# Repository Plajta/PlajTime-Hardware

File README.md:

# PlajTime Hardware
This repository has the full history of PlajTime hardware development.
Before 19.9.2025 development took place in a single private repository and it was starting to be a little bit messy.
With beginning work on PlajTime's second prototype we made the decision to split the repos and make the code and design finally available.

## What about the older versions?
Every "release" will have it's own tag so you (and we) can look at the older versions and laugh how bad at engineering we are.

## License

This project is licensed under the [Creative Commons Attribution-NonCommercial-ShareAlike 4.0 International License](https://creativecommons.org/licenses/by-nc-sa/4.0/).

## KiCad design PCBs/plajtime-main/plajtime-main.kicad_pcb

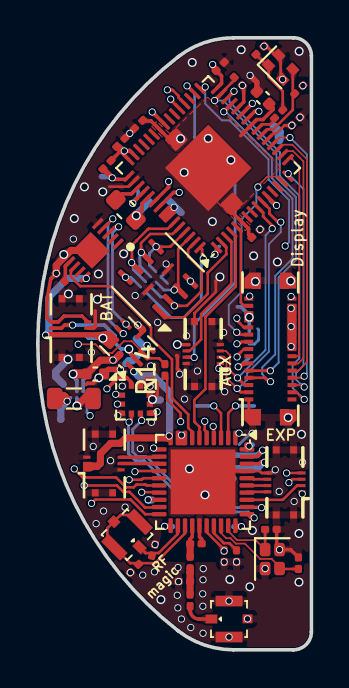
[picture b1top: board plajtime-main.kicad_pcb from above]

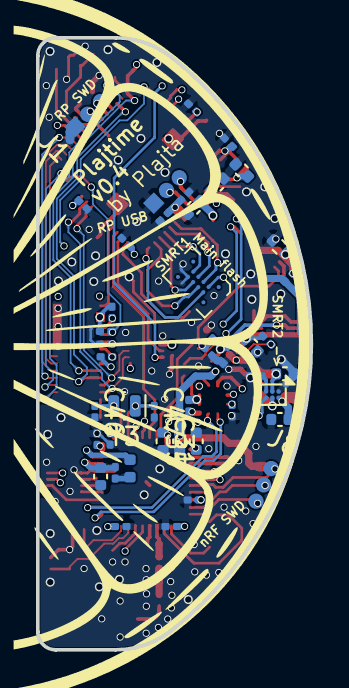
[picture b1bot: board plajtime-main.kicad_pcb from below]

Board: 6 copper layers, 15.2 x 34.0 mm, 85 parts (44 on the bottom side), 80 nets.

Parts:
C1, C6, C8, C9, C12, C17, C31, C35, C41, C43: 4.7uF; C_0402_1005Metric
C2, C29, C42: 1uF; C_0201_0603Metric
C3, C4: 15pF_H; C_0201_0603Metric
C5, C7, C10, C11, C14, C16, C18, C19, C20, C21, C22, C23, C24, C25, C27, C30, C36, C38, C39: 0.1uF; C_0201_0603Metric
C13, C15: 10uF; C_0402_1005Metric
C26: 0.47uF; C_0201_0603Metric
C32, C33: 12pF_H; C_0201_0603Metric
C34: 1.2pF_H; C_0201_0603Metric
C37: 1pF_H; C_0201_0603Metric
C40: 820pF; C_0201_0603Metric
C44, C45: 270pF_H; C_0201_0603Metric
C46, C47: TBD; C_0201_0603Metric
J1: RP SWD; PinHeader_1x03_P1.00mm_Vertical
J2: RP USB; PinHeader_1x03_P1.00mm_Vertical
J4: Display connector; ConnectorDisplay-30
J5: Extention connector; 5050660822
J6, J9: Conn_Coaxial; W.FL_Hirose_W.FL2-R-SMT-1_Vertical
J7: Battery Connector; CONN_505066-0622_MOL
J8: Nordic SWD; PinHeader_1x03_P1.00mm_Vertical_1
J10: Internal connector; 5050660822
J11: USB; CONN_505066-0622_MOL
L1: 3.3uH; L_0603_1608Metric
L2: 1uH; L_0805_2012Metric
L3: 2.2nH; R_0201_0603Metric
L4: 4.7nH; L_0201_0603Metric
L5: 15nH; L_0201_0603Metric
L6: 10uH; L_0402_1005Metric
R1: 7.32k; R_0201_0603Metric
R2: 133k; R_0201_0603Metric
R3: 33; R_0201_0603Metric
R4: 1k; R_0201_0603Metric
R5: 10m; R_0402_1005Metric
R8, R9, R10, R11, R12: 10k; R_0201_0603Metric
R13, R14: TBD; R_0201_0603Metric
U1: W25Q64JWUUIQ; Winbond_USON-8-2EP_3x4mm_P0.8mm_EP0.2x0.8mm
U2: W25Q64JWBYIM; BGA-24_4x6_6.0x6.0mm
U3: TPS628438YKA; Texas_DSBGA-6_0.757x1.01mm_Layout2x3_P0.35mm
U4: MP2664; MPS_MP2664_QFN-10_2x2mm_P0.5mm
U5: RP2350A; QFN-60-1EP_7x7mm_P0.4mm_EP3.4x3.4mm
U6: BMA456; LGA-12_2x2mm_P0.5mm
U7: MAX17055; SON40P250X200X80-11N
U9: nRF52833_QDxx; QFN-40-1EP_5x5mm_P0.4mm_EP3.6x3.6mm
Y1: 13MHz; Oscillator_SMD_Abracon_ASCO-4Pin_1.6x1.2mm
Y2: 32MHz; Crystal_SMD_WE_IQXC-26-4Pin_1.6x1.2mm
Y3: 32.768kHz Crystal; Crystal_SMD_MicroCrystal_CM9V-T1A-2Pin_1.6x1.0mm

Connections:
+1V1: C5.1, C8.1, C9.1, C10.1, L1.1, U5.6 (DVDD), U5.23 (DVDD), U5.39 (DVDD), U5.50 (VREG_FB)
+3V: C6.1, C11.1, C14.1, C15.1, C16.1, C18.1, C19.1, C20.1, C21.1, C23.1, C24.1, C25.1, C27.1, C29.1, C30.1, C31.1, C36.1, J4.11, J4.23, J4.25, J4.29, J4.30, J5.1, J10.1, L2.2, R3.1, R8.1, R9.1, R10.1, R11.1, U1.8 (VCC), U2.B2 (VCC), U3.A2 (VOS), U5.1 (IOVDD), U5.11 (IOVDD), U5.20 (IOVDD), U5.26 (RUN), U5.30 (IOVDD), U5.38 (IOVDD), U5.44 (ADC_AVDD), U5.45 (IOVDD), U5.49 (VREG_VIN), U5.53 (USB_OTP_VDD), U5.54 (QSPI_IOVDD), U6.3 (VDDIO), U6.7 (VDD), U6.10 (CSB), U9.8 (VDD), U9.9 (VDDH), U9.18 (VDD), U9.30 (VDD), U9.40 (VDD)
+5V: C2.1, C41.1, J11.1, J11.3, U4.1 (IN), U9.10 (VBUS)
+BATT: C17.1, C22.1, J7.1, J7.2, R13.1, U4.8 (BATT), U4.9 (BATT), U7.10 (BATT)
-BATT: C22.2, C26.2, J7.5, J7.6, R5.1, U7.6 (CSP), U7.11 (CSP)
/BATT_NTC: J7.3, R1.2, U4.2 (NTC)
/CHARGER_INT: R14.1, U9.17 (P0.20)
/CHG_VDD: C7.1, R1.1, U4.4 (VDD)
/DEC_4_6: C42.1, C43.1, L5.1, U9.26 (DEC6), U9.38 (DEC4)
/DISP_CS: J4.6, U5.15 (GPIO11)
/DISP_DI1: J4.12, U5.17 (GPIO13)
/DISP_DI2: J4.10, U5.18 (GPIO14)
/DISP_DI3: J4.8, U5.19 (GPIO15)
/DISP_DIO0: J4.14, U5.16 (GPIO12)
/DISP_EN: J4.21, R9.2, U5.31 (GPIO19)
/DISP_IM0: J4.17, R12.1
/DISP_IM1: J4.15, R10.2
/DISP_RST: J4.19, R8.2, U5.14 (GPIO10)
/DISP_SCL: J4.4, U5.28 (GPIO17)
/DISP_TE: J4.27, U5.5 (GPIO3)
/EXT_GPIO_1: J5.6, U9.36 (AIN7/P0.31)
/EXT_GPIO_2: J5.3, U9.33 (AIN4/P0.28)
/EXT_INT: J5.2, U9.34 (AIN5/P0.29)
/EXT_RST: J5.4, U9.35 (AIN6/P0.30)
/GAUGE_INT: U7.8 (ALRT), U9.7 (P0.11)
/IMU_INT_1: U6.5 (INT1), U9.31 (AIN1/P0.03)
/IMU_INT_2: U6.6 (INT2), U9.32 (AIN0/P0.02)
/NRF_DECUSB: C35.1, U9.11 (DECUSB)
/NRF_SWDCLK: J8.2, U9.19 (SWDIO)
/NRF_SWDIO: J8.3, U9.20 (SWDCLK)
/NRF_SWDRST: J8.1, U9.16 (P0.18/~RESET)
/NRF_XL1: C46.1, U9.2 (XL1/P0.00), Y3.2
/NRF_XL2: C47.1, U9.3 (XL2/P0.01), Y3.1
/QMI_CS0: U2.B3 (~CS), U5.60 (QSPI_SS)
/QMI_CS1: U1.1 (~CS), U5.2 (GPIO0)
/QMI_SCLK: U1.6 (CLK), U2.D2 (CLK), U5.56 (QSPI_SCLK)
/QMI_SD0: U1.5 (DI/IO_{0}), U2.E2 (DI/IO_{0}), U5.57 (QSPI_SD0)
/QMI_SD1: U1.2 (DO/IO_{1}), U2.C3 (DO/IO_{1}), U5.59 (QSPI_SD1)
/QMI_SD2: U1.3 (~WP/IO_{2}), U2.D3 (~WP/IO_{2}), U5.58 (QSPI_SD2)
/QMI_SD3: U1.7 (~HOLD/~RESET/IO_{3}), U2.C2 (~HOLD/~RESET/IO_{3}), U5.55 (QSPI_SD3)
/RP_SWDCLK: J1.2, U5.24 (SWCLK)
/RP_SWDIO: J1.3, U5.25 (SWDIO)
/RP_USB_D+: J2.2, U5.52 (USB_DP)
/RP_USB_D-: J2.3, U5.51 (USB_DM)
/SLIDER_INT: J10.6, U5.3 (GPIO1)
/TP_INT: J4.7, U5.27 (GPIO16)
/TP_RESET: J4.9, R11.2, U5.29 (GPIO18)
/VIC_INT: J10.4, U5.32 (GPIO20)
/XIN: C3.1, U5.21 (XIN), Y1.3
/XOUT: R4.2, U5.22 (XOUT)
GND: C1.2, C2.2, C3.2, C4.2, C5.2, C6.2, C7.2, C8.2, C9.2, C10.2, C11.2, C12.2, C13.2, C14.2, C15.2, C16.2, C17.2, C18.2, C19.2, C20.2, C21.2, C23.2, C24.2, C25.2, C27.2, C29.2, C30.2, C31.2, C32.2, C33.2, C34.2, C35.2, C36.2, C37.2, C38.2, C39.2, C40.2, C41.2, C42.2, C43.2, C44.2, C45.2, C46.2, C47.2, J1.1, J2.1, J4.1, J4.16, J4.18, J4.20, J4.22, J4.24, J4.26, J4.28, J4.31 (MP), J5.8, J5.MP (MountPin), J6.2 (Ext), J7.4, J7.MP (MountPin), J10.2, J10.7, J10.MP (MountPin), J11.2, J11.5, J11.MP (MountPin), R2.2, R5.2, R12.2, U1.4 (GND), U1.9 (EP), U2.E3 (GND), U3.A1 (GND), U4.5 (GND), U5.47 (VREG_PGND), U5.61 (GND), U6.1 (SDO), U6.4 (ASDA), U6.8 (GNDIO), U6.9 (GND), U6.11 (ASCL), U7.5 (CSN), U9.25 (VSS_PA), U9.37 (VSS), U9.41 (VSS), Y1.2 (G), Y1.4 (G), Y2.2 (G), Y2.4 (G)
GPU_INT: U5.4 (GPIO2), U9.6 (P1.09)
unnamed: C4.1, R4.1, Y1.1
unnamed: C26.1, U7.7 (REG)
unnamed: C34.1, L3.2, L4.1
unnamed: J6.1 (In), L3.1
unnamed: C45.1, J9.2 (Ext), U9.23 (NFC2/P0.10)
unnamed: C44.1, J9.1 (In), U9.22 (NFC1/P0.09)
unnamed: L5.2, L6.1
unnamed: L2.1, U3.B2 (SW)
unnamed: R2.1, U3.C1 (VSET)
unnamed: R13.2, R14.2, U4.3 (INT)
unnamed: C12.1, R3.2, U5.46 (VREG_AVDD)
unnamed: L1.2, U5.48 (VREG_LX)
unnamed: C37.1, L4.2, U9.24 (ANT)
unnamed: L6.2, U9.39 (DCC)
unnamed: C39.1, U9.1 (DEC1)
unnamed: C38.1, U9.27 (DEC3)
unnamed: C40.1, U9.21 (DEC5)
unnamed: C32.1, U9.28 (XC1), Y2.3
unnamed: C33.1, U9.29 (XC2), Y2.1
RP_SCL: J4.3, J10.3, U5.10 (GPIO7)
RP_SDA: J4.5, J10.5, U5.9 (GPIO6)
SCL: J5.7, U4.6 (SCL), U6.12 (SCX), U7.3 (SCL), U9.4 (AIN2/P0.04)
SDA: J5.5, U4.7 (SDA), U6.2 (SDX), U7.4 (SDA), U9.5 (AIN3/P0.05)
UART_RX: U5.35 (GPIO23), U9.15 (P0.17)
UART_TX: U5.34 (GPIO22), U9.14 (P0.15)
USB_D+: J11.6, U9.12 (D-)
USB_D-: J11.4, U9.13 (D+)
VSYS: C1.1, C13.1, J10.8, U3.B1 (VIN), U3.C2 (EN), U4.10 (SYS)

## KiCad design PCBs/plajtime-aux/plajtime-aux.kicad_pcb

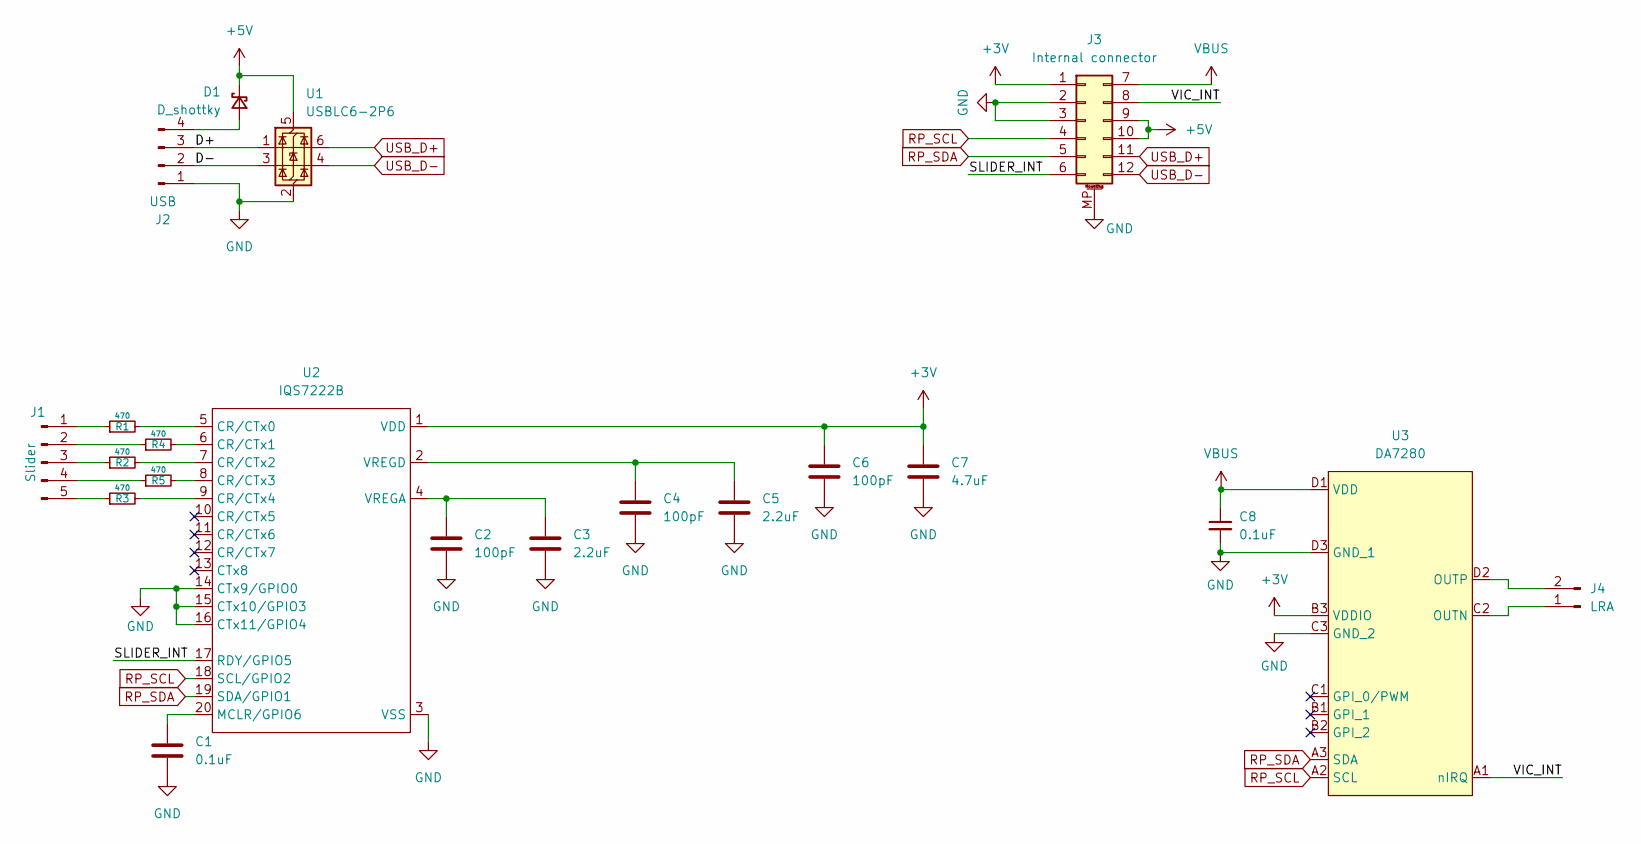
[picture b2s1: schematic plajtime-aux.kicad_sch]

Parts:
C1, C8: 0.1uF; C_0201_0603Metric; LCSC_Part C161494
C2, C4, C6: 100pF; C_0201_0603Metric; LCSC_Part C541236
C3, C5: 2.2uF; C_0201_0603Metric; Mouser 81-GRM033R61A225KE7D
C7: 4.7uF; C_0402_1005Metric; LCSC_Part C23733
D1: D_shottky; D_0402_1005Metric; LCSC_Part C94366
J1: Slider; TouchSlider-5_25.0248x4.2mm
J2: USB; PinHeader_1x04_P2.54mm_Vertical
J3: Internal connector; 5050701222; Mouser 538-505070-1222
J4: LRA; PinHeader_1x02_P1.00mm_Vertical
R1, R2, R3, R4, R5: 470; R_0201_0603Metric; LCSC_Part C18164334
U1: USBLC6-2P6; PESD3V3L5UF115; LCSC_Part C478118
U2: IQS7222B; QFN-20-1EP_3x3mm_P0.4mm_EP1.65x1.65mm; Mouser 957-IQS7222B102QNR
U3: DA7280; BGA12C40P3X4_135X175X58; Mouser 724-DA7280-00V42

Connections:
+3V: C6.1, C7.1, J3.1, U2.1 (VDD), U3.B3 (VDDIO)
+5V: D1.1 (K), J3.9, J3.10, U1.5 (VBUS)
/D+: J2.3, U1.1 (I/O1)
/D-: J2.2, U1.3 (I/O2)
/SLIDER_INT: J3.6, U2.17 (RDY/GPIO5)
/VIC_INT: J3.8, U3.A1 (nIRQ)
GND: C1.2, C2.2, C3.2, C4.2, C5.2, C6.2, C7.2, C8.2, J2.1, J3.2, J3.3, J3.MP (MountPin), U1.2 (GND), U2.3 (VSS), U2.14 (CTx9/GPIO0), U2.15 (CTx10/GPIO3), U2.16 (CTx11/GPIO4), U2.21 (EP), U3.C3 (GND_2), U3.D3 (GND_1)
unnamed: D1.2 (A), J2.4
unnamed: J1.1, R1.1
unnamed: J1.2, R4.1
unnamed: J1.3, R2.1
unnamed: J1.4, R5.1
unnamed: J1.5, R3.1
unnamed: J4.1, U3.C2 (OUTN)
unnamed: J4.2, U3.D2 (OUTP)
unnamed: R1.2, U2.5 (CR/CTx0)
unnamed: R4.2, U2.6 (CR/CTx1)
unnamed: R2.2, U2.7 (CR/CTx2)
unnamed: R5.2, U2.8 (CR/CTx3)
unnamed: R3.2, U2.9 (CR/CTx4)
unnamed: C1.1, U2.20 (MCLR/GPIO6)
unnamed: C2.1, C3.1, U2.4 (VREGA)
unnamed: C4.1, C5.1, U2.2 (VREGD)
RP_SCL: J3.4, U2.18 (SCL/GPIO2), U3.A2 (SCL)
RP_SDA: J3.5, U2.19 (SDA/GPIO1), U3.A3 (SDA)
USB_D+: J3.11, U1.6 (I/O1)
USB_D-: J3.12, U1.4 (I/O2)
VBUS: C8.1, J3.7, U3.D1 (VDD)

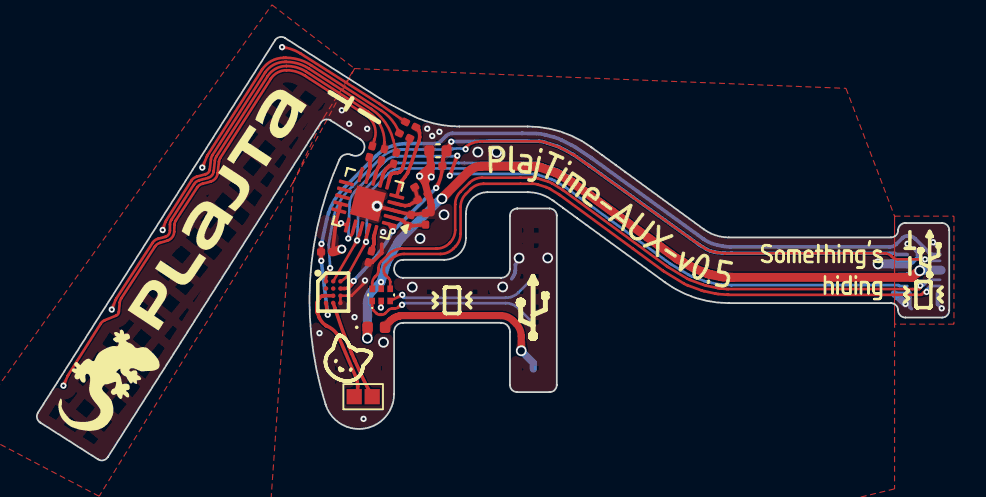
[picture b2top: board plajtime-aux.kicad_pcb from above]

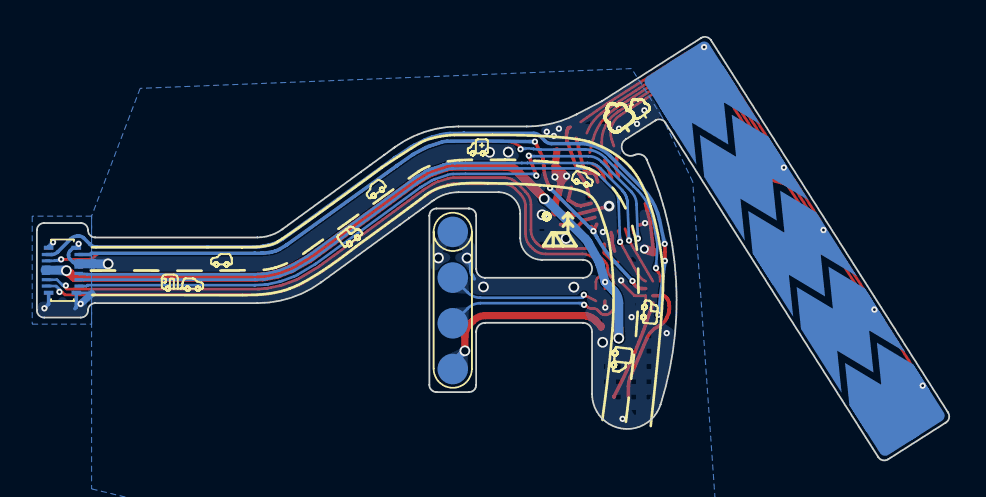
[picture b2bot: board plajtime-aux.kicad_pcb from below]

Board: 2 copper layers, 50.7 x 23.5 mm, 21 parts (3 on the bottom side), 28 nets.

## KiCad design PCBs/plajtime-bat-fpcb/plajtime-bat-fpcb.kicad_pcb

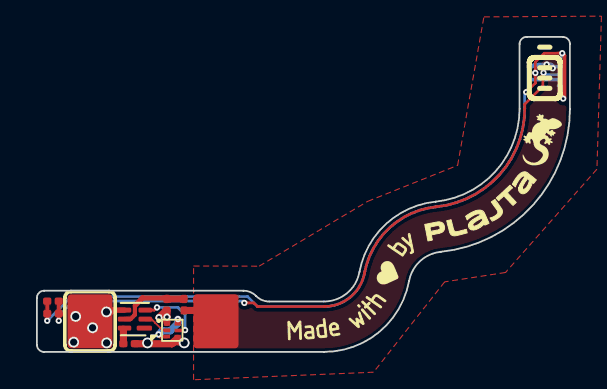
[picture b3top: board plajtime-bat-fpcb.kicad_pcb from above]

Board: 2 copper layers, 29.6 x 17.5 mm, 9 parts (1 on the bottom side), 10 nets.

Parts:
BT1: Battery_Cell; Battery
C1: 0.1uF; C_0201_0603Metric
J7: Battery Connector; CONN_505070-0622_MOL
Q1: NX7002BKXBZ; DFN1010B-6
R1: 330; R_0201_0603Metric
R2: 2.2k; R_0201_0603Metric
R3: 26.1k; R_0201_0603Metric
TH1: Thermistor_NTC; R_0201_0603Metric
U1: BQ297xy; WSON-6_1.5x1.5mm_P0.5mm

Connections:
+BATT: BT1.1 (+), J7.1, J7.2, R1.1
-BATT: J7.5, J7.6, Q1.4 (S), R2.2
-CELL: BT1.2 (-), C1.2, Q1.1 (S), U1.4 (VSS)
/BATT_NTC: J7.3, R3.2, TH1.1
GND: J7.4, J7.MP (MountPin), R3.1, TH1.2
unnamed: Q1.3 (D), Q1.6 (D)
unnamed: Q1.2 (G), U1.2 (Cout)
unnamed: Q1.5 (G), U1.3 (Dout)
unnamed: C1.1, R1.2, U1.5 (BAT)
unnamed: R2.1, U1.6 (V-)

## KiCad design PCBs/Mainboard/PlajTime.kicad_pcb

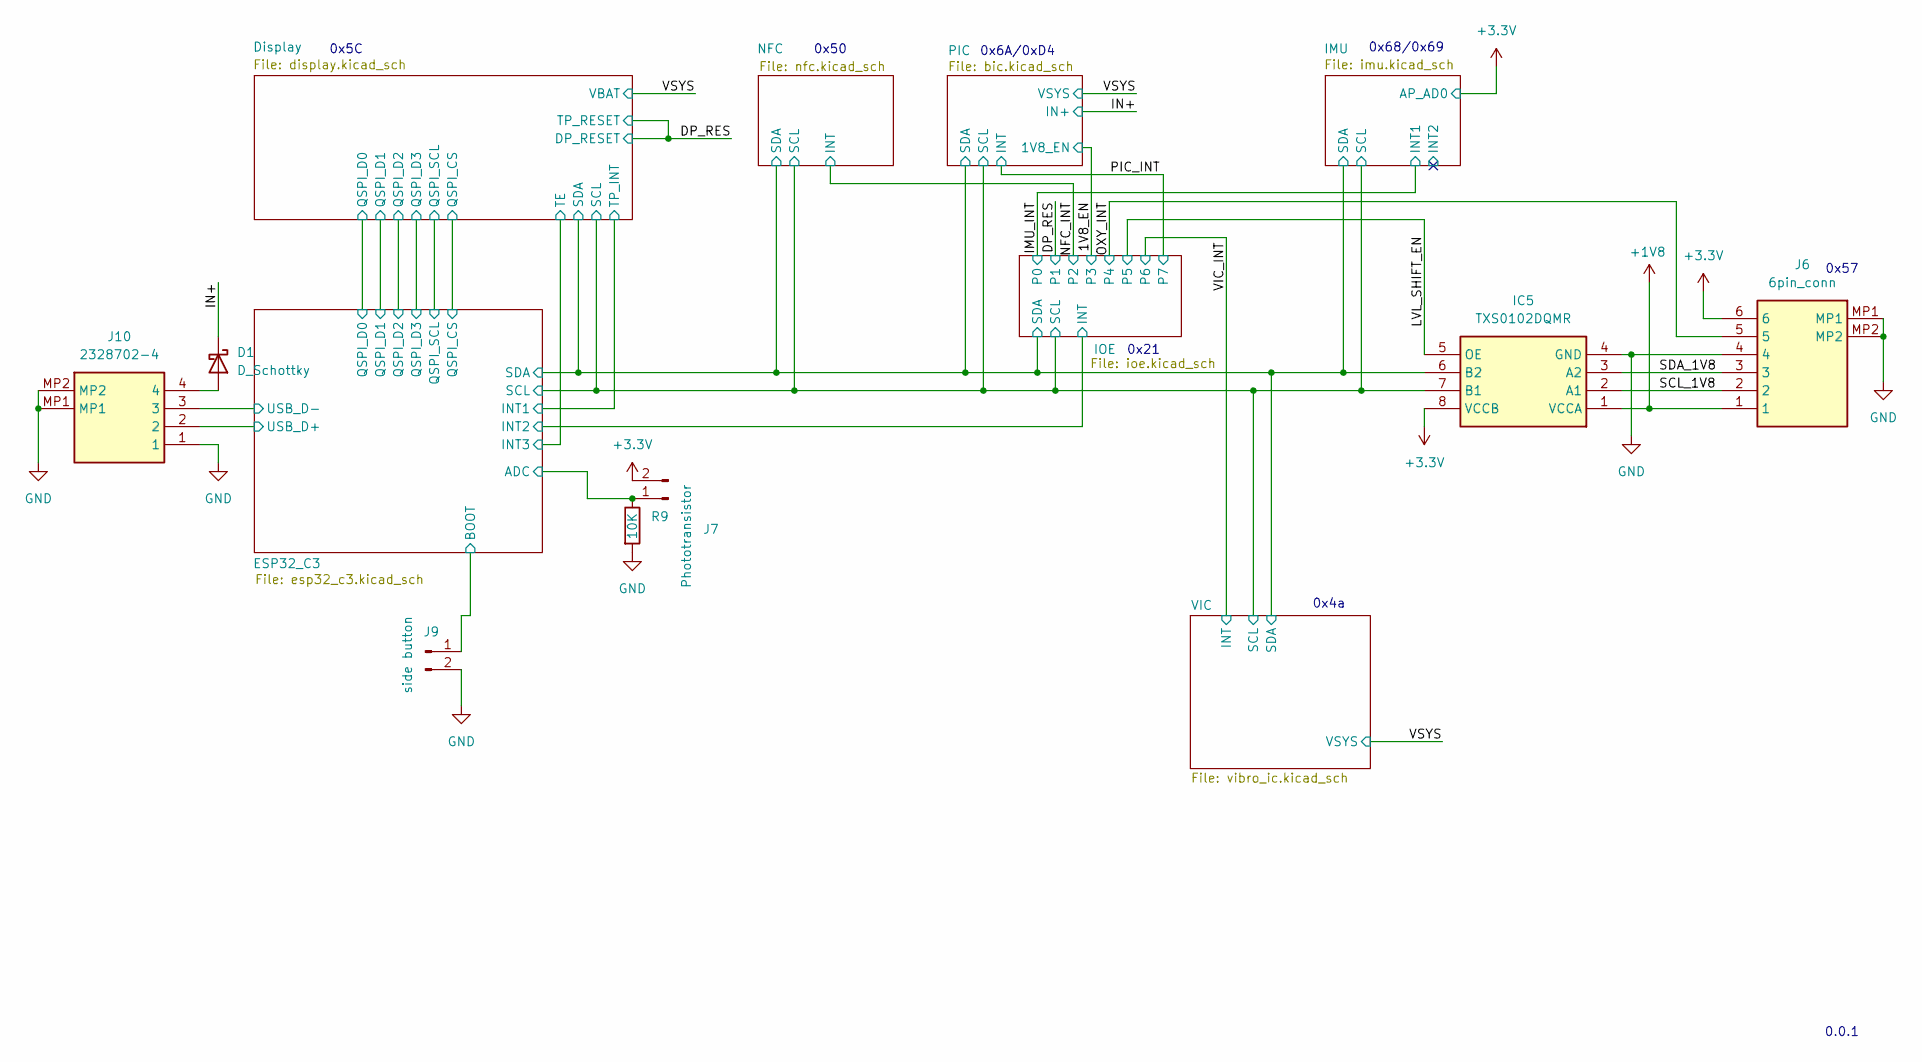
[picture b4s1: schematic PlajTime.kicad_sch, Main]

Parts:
D1: D_Schottky; D_0603_1608Metric
IC5: TXS0102DQMR; SON40P120X180X40-8N; Mouser Part Number 595-TXS0102DQMR
J6: 6pin_conn; Mouser Part Number 571-2328702-6
J7: Phototransistor; PinHeader_1x02_P1.00mm_Vertical
J9: side button; PinHeader_1x02_P1.00mm_Vertical
J10: 2328702-4; 23287024; Mouser Part Number 571-2328702-4
R9: 10K; R_0201_0603Metric

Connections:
+1V8: IC5.1 (VCCA), J6.1; also elsewhere on the board
+3.3V: IC5.8 (VCCB), J6.6, J7.2; also elsewhere on the board
/Display/SCL: IC5.7 (B1); also elsewhere on the board
/Display/SDA: IC5.6 (B2); also elsewhere on the board
/ESP32_C3/ADC: J7.1, R9.1; also elsewhere on the board
/ESP32_C3/BOOT: J9.1; also elsewhere on the board
/ESP32_C3/USB_D+: J10.2; also elsewhere on the board
/ESP32_C3/USB_D-: J10.3; also elsewhere on the board
/IN+: D1.1 (K); also elsewhere on the board
/LVL_SHIFT_EN: IC5.5 (OE); also elsewhere on the board
/OXY_INT: J6.5; also elsewhere on the board
/SCL_1V8: IC5.2 (A1), J6.2
/SDA_1V8: IC5.3 (A2), J6.3
GND: IC5.4 (GND), J6.4, J6.MP1, J6.MP2, J9.2, J10.1, J10.MP1, J10.MP2, R9.2; also elsewhere on the board
unnamed: D1.2 (A), J10.4

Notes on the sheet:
0.0.1
0x21
0x5C
0x68/0x69
0x57
0x6A/0xD4
0x4a
0x50

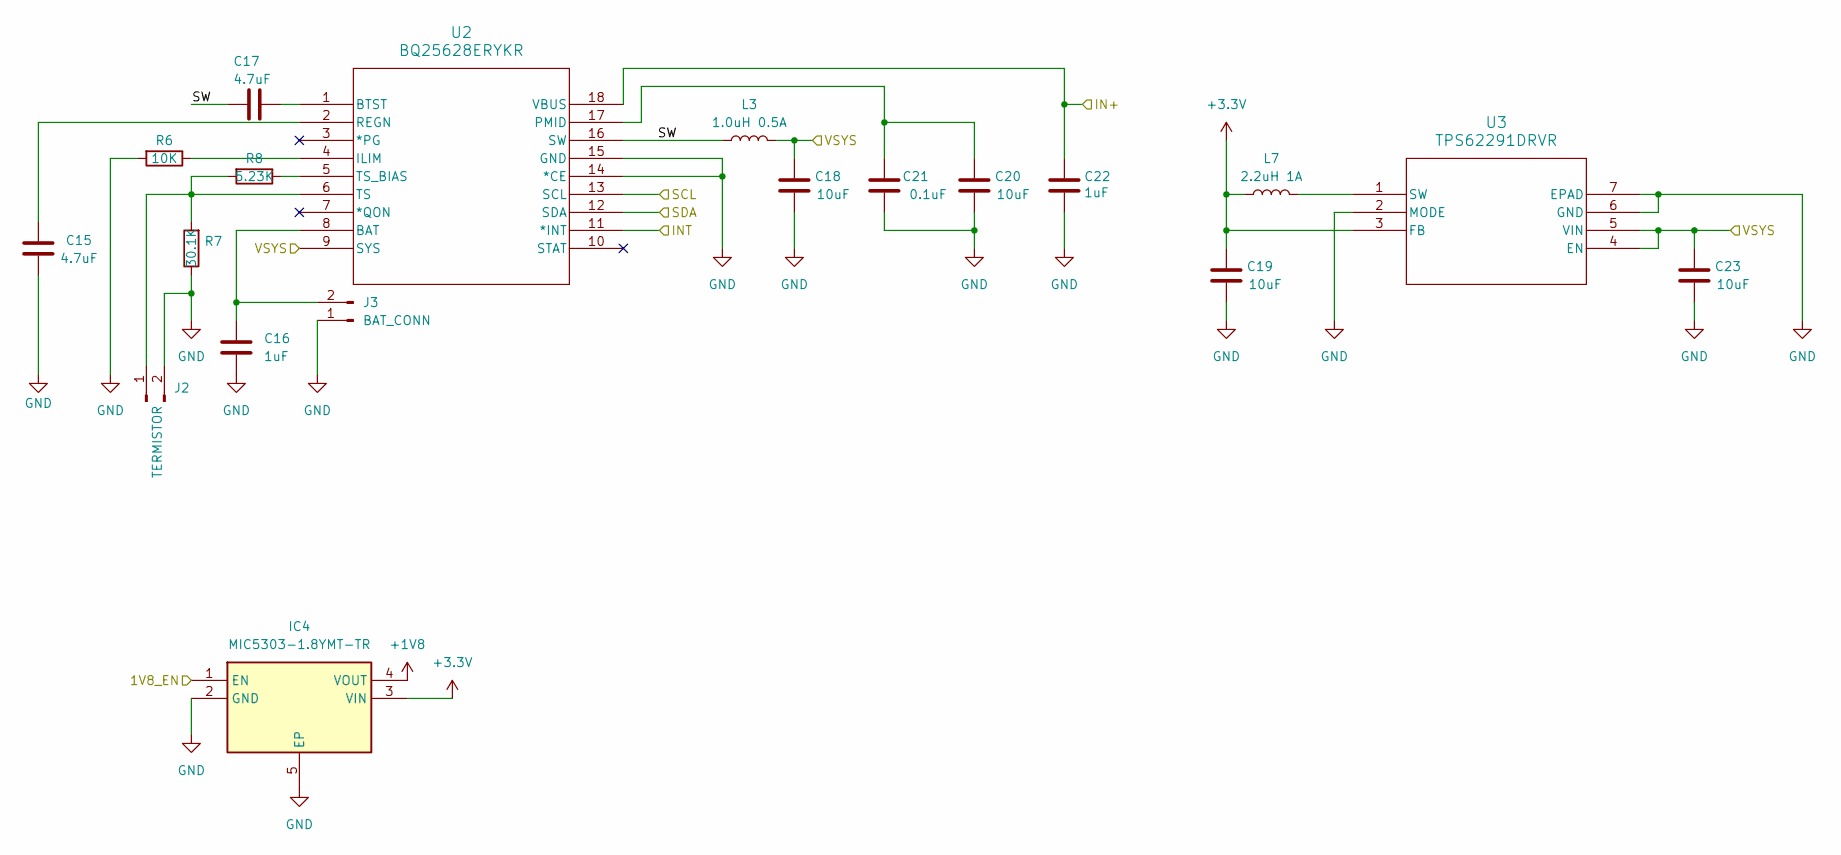
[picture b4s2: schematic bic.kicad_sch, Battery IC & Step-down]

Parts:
C15, C17: 4.7uF; C_0201_0603Metric
C16, C22: 1uF; C_0201_0603Metric
C18, C19, C20, C23: 10uF; C_0402_1005Metric
C21: 0.1uF; C_0201_0603Metric
IC4: MIC5303-1.8YMT-TR; SON50P160X120X60-5N-D; Mouser Part Number 998-MIC5303-1.8YMTTR
J2: TERMISTOR; PinHeader_1x02_P1.00mm_Vertical
J3: BAT_CONN; BattSolderPads
L3: 1.0uH 0.5A; L_0402_1005Metric
L7: 2.2uH 1A; L_0603_1608Metric
R6: 10K; R_0201_0603Metric
R7: 30.1K; R_0201_0603Metric
R8: 5.23K; R_0201_0603Metric
U2: BQ25628ERYKR; WQFN-HR18__RYK_TEX
U3: TPS62291DRVR; DRV6_1P6X1

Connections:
+1V8: IC4.4 (VOUT); also elsewhere on the board
+3.3V: C19.1, IC4.3 (VIN), L7.1, U3.3 (FB); also elsewhere on the board
/1V8_EN: IC4.1 (EN); also elsewhere on the board
/Display/SCL: U2.13 (SCL); also elsewhere on the board
/Display/SDA: U2.12 (SDA); also elsewhere on the board
/IN+: C22.1, U2.18 (VBUS); also elsewhere on the board
/PIC/SW: C17.1, L3.1, U2.16 (SW)
/PIC_INT: U2.11 (*INT); also elsewhere on the board
/VSYS: C18.1, C23.1, L3.2, U2.9 (SYS), U3.4 (EN), U3.5 (VIN); also elsewhere on the board
GND: C15.1, C16.2, C18.2, C19.2, C20.2, C21.2, C22.2, C23.2, IC4.2 (GND), IC4.5 (EP), J2.2, J3.1, R6.2, R7.1, U2.14 (*CE), U2.15 (GND), U3.2 (MODE), U3.6 (GND), U3.7 (EPAD); also elsewhere on the board
unnamed: J2.1, R7.2, R8.2, U2.6 (TS)
unnamed: C16.1, J3.2, U2.8 (BAT)
unnamed: C17.2, U2.1 (BTST)
unnamed: R6.1, U2.4 (ILIM)
unnamed: C20.1, C21.1, U2.17 (PMID)
unnamed: C15.2, U2.2 (REGN)
unnamed: R8.1, U2.5 (TS_BIAS)
unnamed: L7.2, U3.1 (SW)

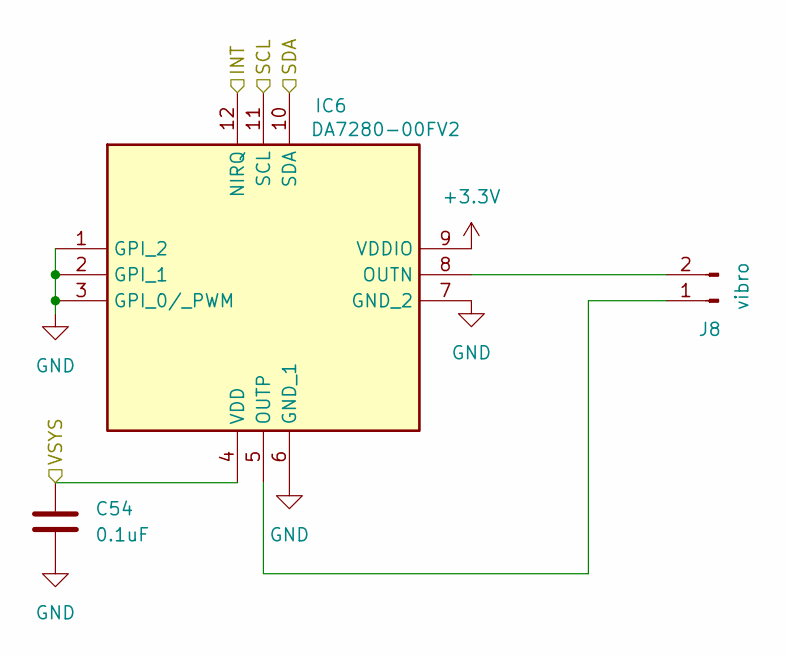
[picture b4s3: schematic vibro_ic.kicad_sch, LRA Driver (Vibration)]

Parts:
C54: 0.1uF; C_0201_0603Metric
IC6: DA7280-00FV2; QFN65P300X300X84-12N; Mouser Part Number 724-DA7280-00FV2
J8: vibro; PinHeader_1x02_P1.00mm_Vertical

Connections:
+3.3V: IC6.9 (VDDIO); also elsewhere on the board
/Display/SCL: IC6.11 (SCL); also elsewhere on the board
/Display/SDA: IC6.10 (SDA); also elsewhere on the board
/VIC_INT: IC6.12 (NIRQ); also elsewhere on the board
/VSYS: C54.1, IC6.4 (VDD); also elsewhere on the board
GND: C54.2, IC6.1 (GPI_2), IC6.2 (GPI_1), IC6.3 (GPI_0/_PWM), IC6.6 (GND_1), IC6.7 (GND_2); also elsewhere on the board
unnamed: IC6.8 (OUTN), J8.2
unnamed: IC6.5 (OUTP), J8.1

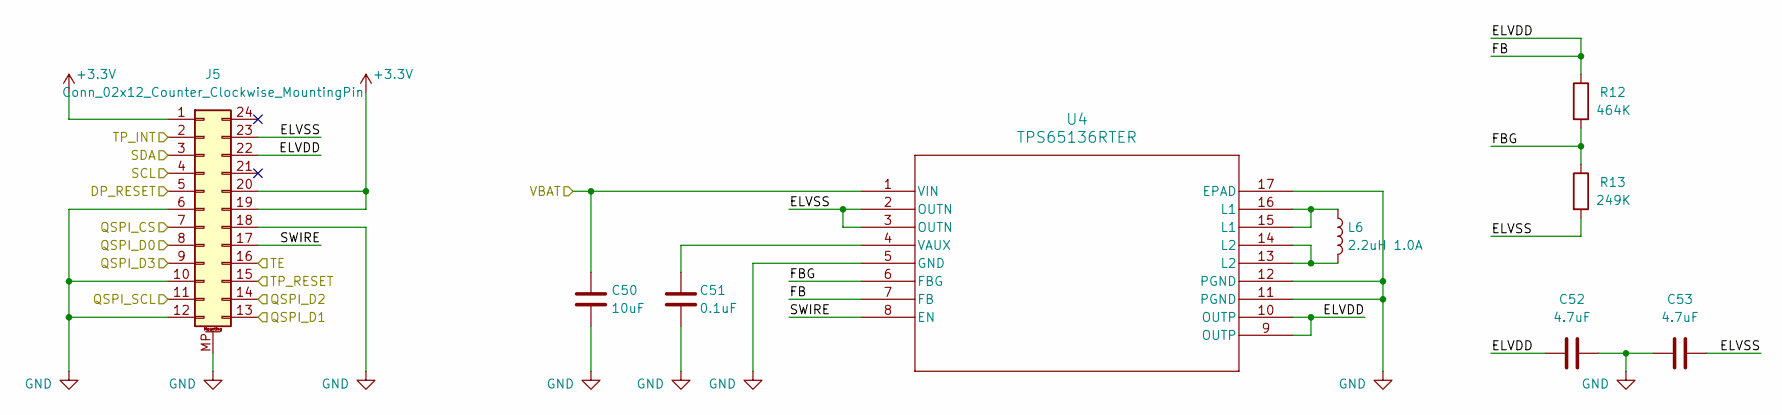
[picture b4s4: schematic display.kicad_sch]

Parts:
C50: 10uF; C_0402_1005Metric
C51: 0.1uF; C_0201_0603Metric
C52, C53: 4.7uF; C_0201_0603Metric
J5: Conn_02x12_Counter_Clockwise_MountingPin; CONN-SMD_24P-P0.40_OK-14GF024-04_2.1INCH
L6: 2.2uH 1.0A; L_0603_1608Metric
R12: 464K; R_0201_0603Metric
R13: 249K; R_0201_0603Metric
U4: TPS65136RTER; RTE16_1P7X1P7

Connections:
+3.3V: J5.1, J5.19, J5.20; also elsewhere on the board
/DP_RES: J5.5, J5.15; also elsewhere on the board
/Display/ELVDD: C52.2, J5.22, R12.1, U4.7 (FB), U4.9 (OUTP), U4.10 (OUTP)
/Display/ELVSS: C53.2, J5.23, R13.2, U4.2 (OUTN), U4.3 (OUTN)
/Display/FBG: R12.2, R13.1, U4.6 (FBG)
/Display/QSPI_CS: J5.7; also elsewhere on the board
/Display/QSPI_D0: J5.8; also elsewhere on the board
/Display/QSPI_D1: J5.13; also elsewhere on the board
/Display/QSPI_D2: J5.14; also elsewhere on the board
/Display/QSPI_D3: J5.9; also elsewhere on the board
/Display/QSPI_SCL: J5.11; also elsewhere on the board
/Display/SCL: J5.4; also elsewhere on the board
/Display/SDA: J5.3; also elsewhere on the board
/Display/SWIRE: J5.17, U4.8 (EN)
/Display/TE: J5.16; also elsewhere on the board
/Display/TP_INT: J5.2; also elsewhere on the board
/VSYS: C50.2, U4.1 (VIN); also elsewhere on the board
GND: C50.1, C51.1, C52.1, C53.1, J5.6, J5.10, J5.12, J5.18, J5.MP (MountPin), U4.5 (GND), U4.11 (PGND), U4.12 (PGND), U4.17 (EPAD); also elsewhere on the board
unnamed: L6.1, U4.15 (L1), U4.16 (L1)
unnamed: L6.2, U4.13 (L2), U4.14 (L2)
unnamed: C51.2, U4.4 (VAUX)

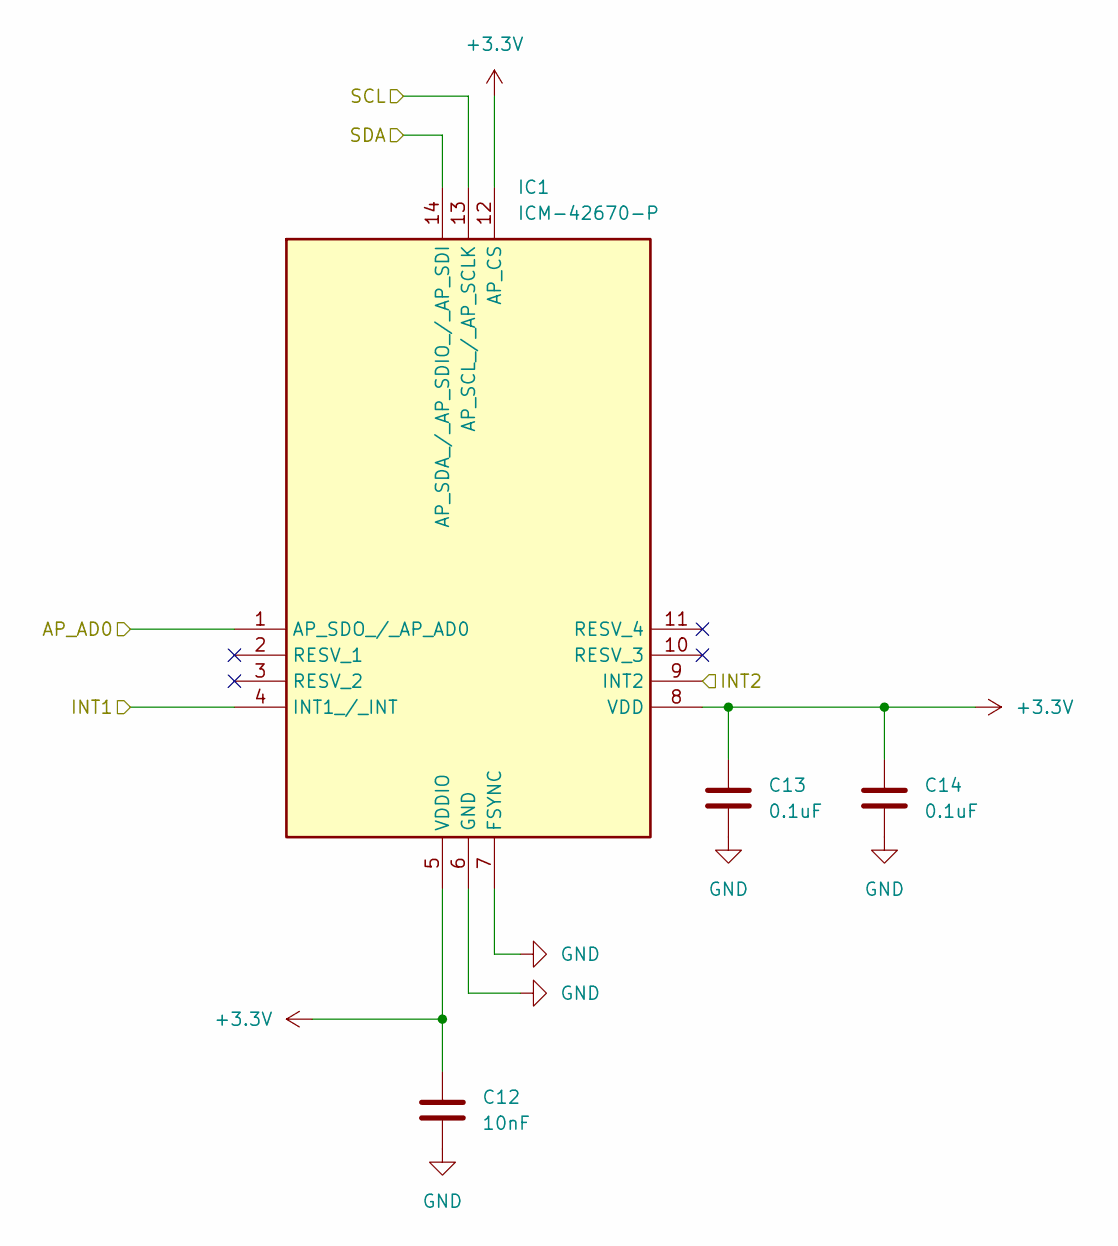
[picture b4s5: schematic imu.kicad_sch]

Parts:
C12: 10nF; C_0201_0603Metric
C13, C14: 0.1uF; C_0201_0603Metric
IC1: ICM-42670-P; ICM42670P; Mouser Part Number 410-ICM-42670-P

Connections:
+3.3V: C12.1, C13.1, C14.1, IC1.1 (AP_SDO_/_AP_AD0), IC1.5 (VDDIO), IC1.8 (VDD), IC1.12 (AP_CS); also elsewhere on the board
/Display/SCL: IC1.13 (AP_SCL_/_AP_SCLK); also elsewhere on the board
/Display/SDA: IC1.14 (AP_SDA_/_AP_SDIO_/_AP_SDI); also elsewhere on the board
/IMU/INT2: IC1.9 (INT2)
/IMU_INT: IC1.4 (INT1_/_INT); also elsewhere on the board
GND: C12.2, C13.2, C14.2, IC1.6 (GND), IC1.7 (FSYNC); also elsewhere on the board

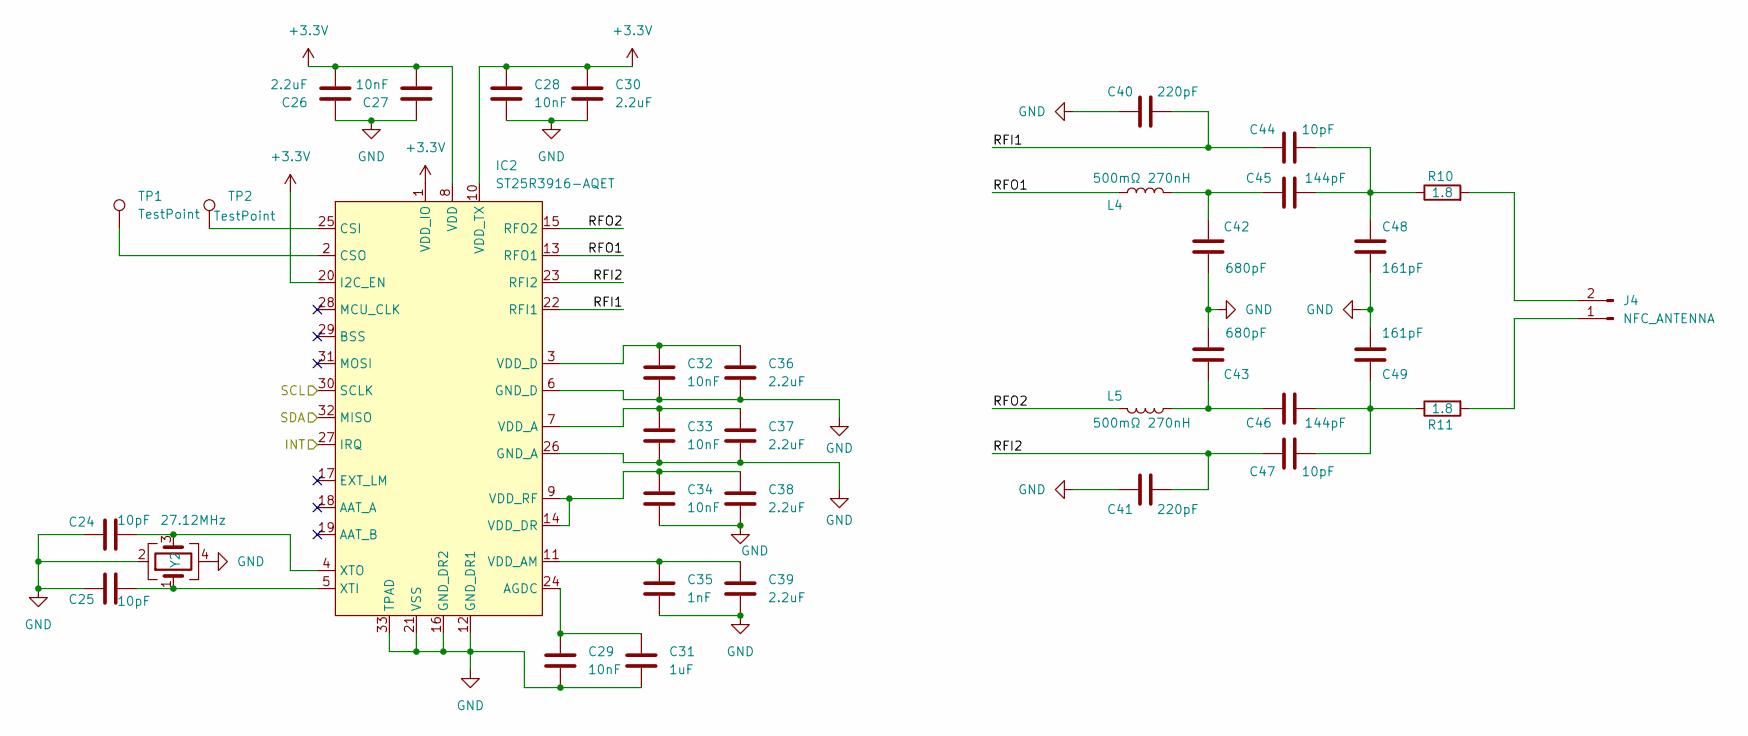
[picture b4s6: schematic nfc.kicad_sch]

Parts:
C24, C25, C44, C47: 10pF; C_0201_0603Metric
C26, C30, C36, C37, C38, C39: 2.2uF; C_0201_0603Metric
C27, C28, C29, C32, C33, C34: 10nF; C_0201_0603Metric
C31: 1uF; C_0201_0603Metric
C35: 1nF; C_0201_0603Metric
C40, C41: 220pF; C_0201_0603Metric
C42, C43: 680pF; C_0201_0603Metric
C45, C46: 144pF; C_0201_0603Metric
C48, C49: 161pF; C_0201_0603Metric
IC2: ST25R3916-AQET
J4: NFC_ANTENNA; PinHeader_1x02_P1.00mm_Vertical
L4, L5: 500mΩ 270nH; L_0603_1608Metric
R10, R11: 1.8; R_0201_0603Metric
TP1, TP2: TestPoint; TestPoint_Pad_D1.0mm
Y2: 27.12MHz; Oscillator_SMD_Abracon_ASCO-4Pin_1.6x1.2mm

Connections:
+3.3V: C26.2, C27.2, C28.1, C30.1, IC2.1 (VDD_IO), IC2.8 (VDD), IC2.10 (VDD_TX), IC2.20 (I2C_EN); also elsewhere on the board
/Display/SCL: IC2.30 (SCLK); also elsewhere on the board
/Display/SDA: IC2.32 (MISO); also elsewhere on the board
/NFC/RFI1: C40.2, C44.1, IC2.22 (RFI1)
/NFC/RFI2: C41.2, C47.1, IC2.23 (RFI2)
/NFC/RFO1: IC2.13 (RFO1), L4.1
/NFC/RFO2: IC2.15 (RFO2), L5.1
/NFC_INT: IC2.27 (IRQ); also elsewhere on the board
GND: C24.1, C25.2, C26.1, C27.1, C28.2, C29.2, C30.2, C31.2, C32.2, C33.2, C34.2, C35.2, C36.2, C37.2, C38.2, C39.2, C40.1, C41.1, C42.2, C43.2, C48.2, C49.2, IC2.6 (GND_D), IC2.12 (GND_DR1), IC2.16 (GND_DR2), IC2.21 (VSS), IC2.26 (GND_A), IC2.33 (TPAD), Y2.2, Y2.4; also elsewhere on the board
unnamed: C42.1, C45.1, L4.2
unnamed: C43.1, C46.1, L5.2
unnamed: C44.2, C45.2, C48.1, R10.1
unnamed: C46.2, C47.2, C49.1, R11.1
unnamed: C29.1, C31.1, IC2.24 (AGDC)
unnamed: IC2.25 (CSI), TP2.1
unnamed: IC2.2 (CSO), TP1.1
unnamed: C33.1, C37.1, IC2.7 (VDD_A)
unnamed: C35.1, C39.1, IC2.11 (VDD_AM)
unnamed: C32.1, C36.1, IC2.3 (VDD_D)
unnamed: C34.1, C38.1, IC2.9 (VDD_RF), IC2.14 (VDD_DR)
unnamed: C25.1, IC2.5 (XTI), Y2.1
unnamed: C24.2, IC2.4 (XTO), Y2.3
unnamed: J4.1, R11.2
unnamed: J4.2, R10.2

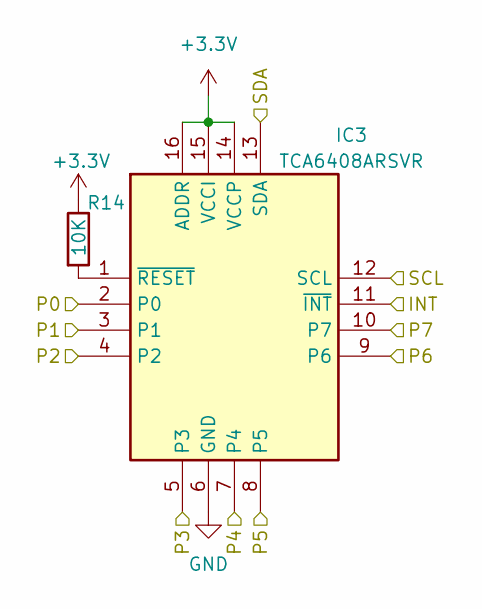
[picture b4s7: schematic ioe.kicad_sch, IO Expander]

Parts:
IC3: TCA6408ARSVR; QFN40P180X260X55-16N; Mouser Part Number 595-TCA6408ARSVR
R14: 10K; R_0201_0603Metric

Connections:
+3.3V: IC3.14 (VCCP), IC3.15 (VCCI), IC3.16 (ADDR), R14.1; also elsewhere on the board
/1V8_EN: IC3.5 (P3); also elsewhere on the board
/DP_RES: IC3.3 (P1); also elsewhere on the board
/Display/SCL: IC3.12 (SCL); also elsewhere on the board
/Display/SDA: IC3.13 (SDA); also elsewhere on the board
/ESP32_C3/INT2: IC3.11 (~INT); also elsewhere on the board
/IMU_INT: IC3.2 (P0); also elsewhere on the board
/LVL_SHIFT_EN: IC3.8 (P5); also elsewhere on the board
/NFC_INT: IC3.4 (P2); also elsewhere on the board
/OXY_INT: IC3.7 (P4); also elsewhere on the board
/PIC_INT: IC3.10 (P7); also elsewhere on the board
/VIC_INT: IC3.9 (P6); also elsewhere on the board
GND: IC3.6 (GND); also elsewhere on the board
unnamed: IC3.1 (~RESET), R14.2
